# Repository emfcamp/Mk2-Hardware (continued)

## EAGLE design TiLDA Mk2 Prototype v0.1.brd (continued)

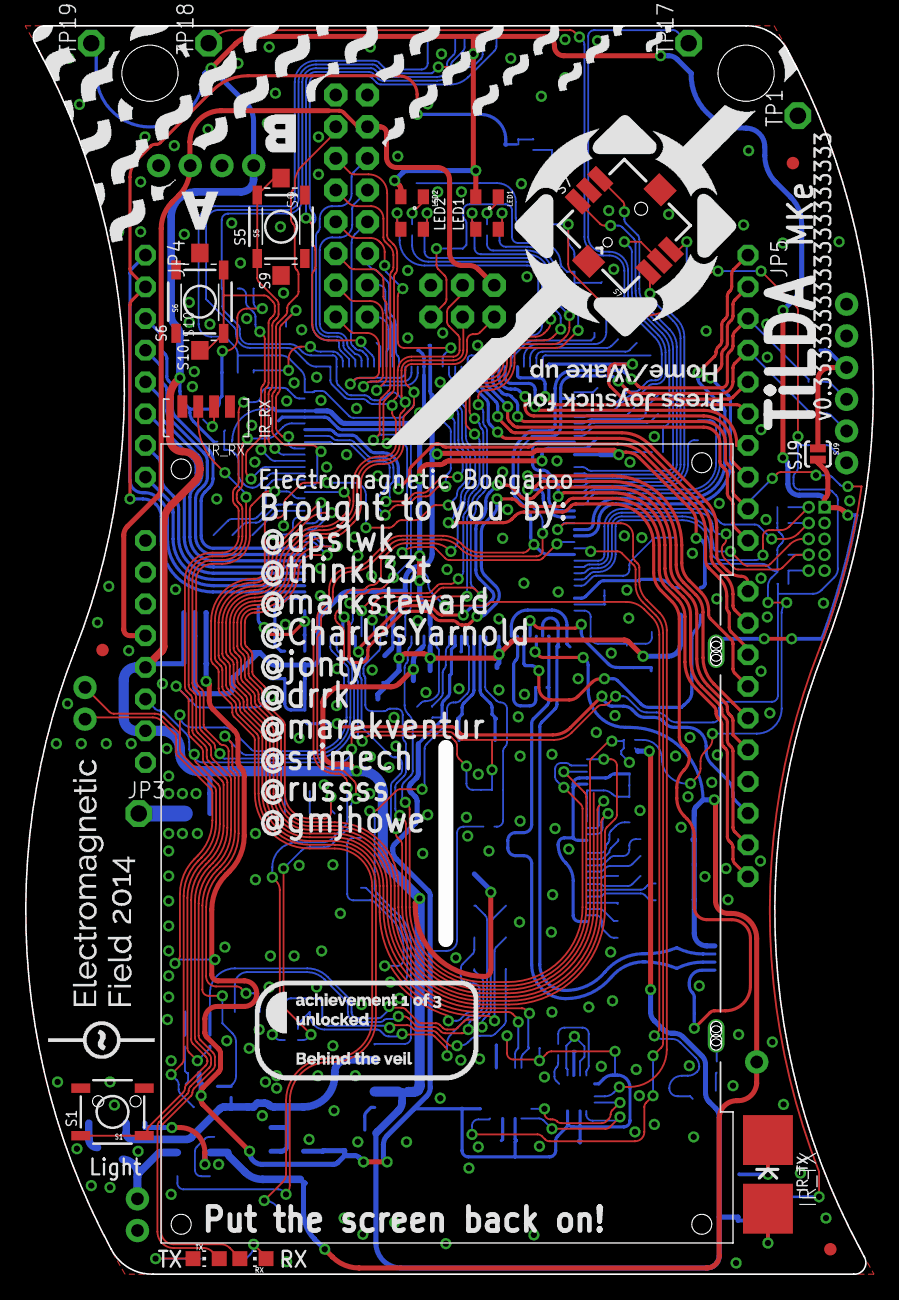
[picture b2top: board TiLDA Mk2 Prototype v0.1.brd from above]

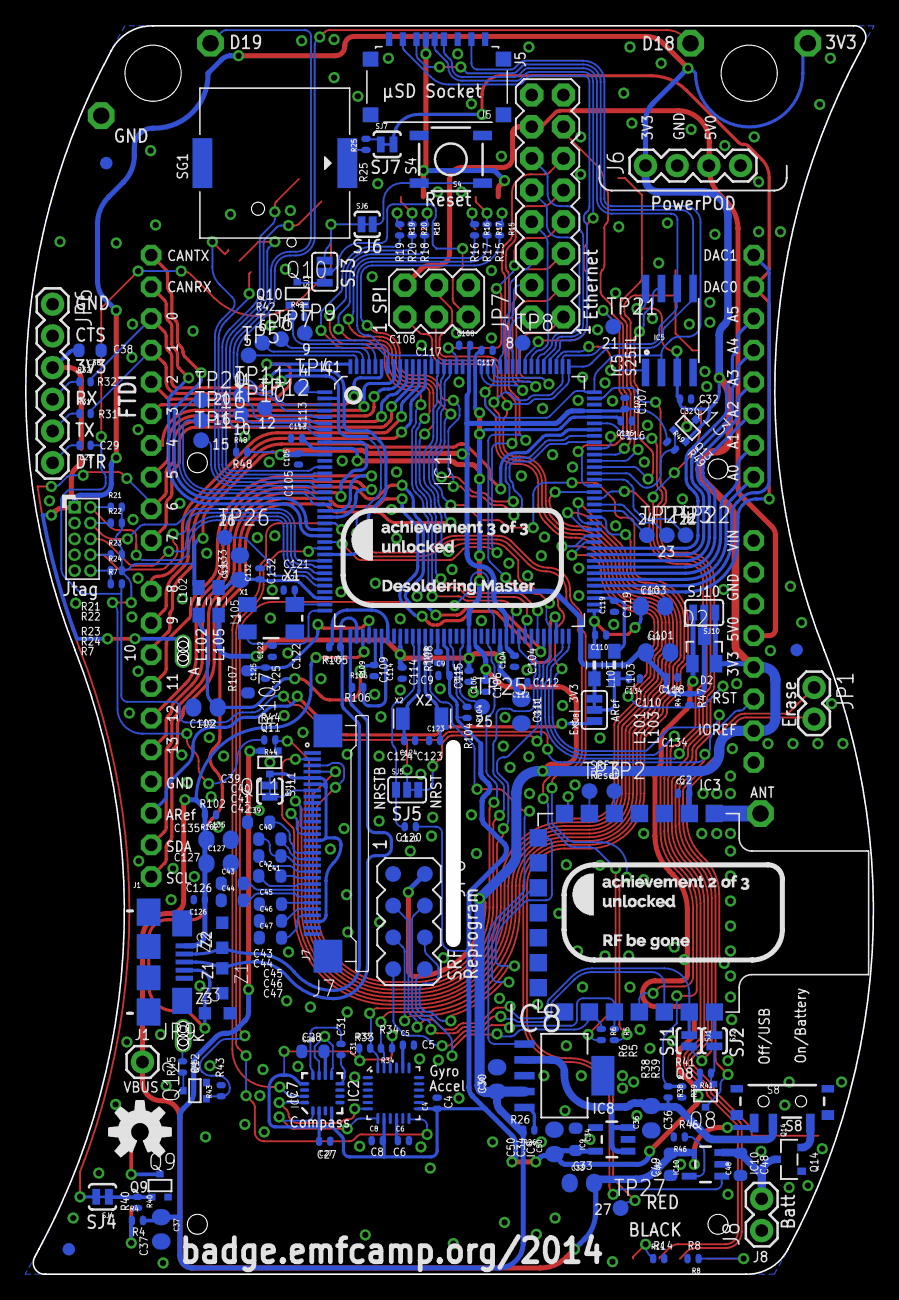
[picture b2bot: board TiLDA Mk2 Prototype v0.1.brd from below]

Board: 4 copper layers, 67.9 x 100.0 mm, 205 parts (177 on the bottom side), 191 nets.

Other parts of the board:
JP9: VBUS; 1X01

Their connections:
VBUS: JP9.1; also elsewhere on the board

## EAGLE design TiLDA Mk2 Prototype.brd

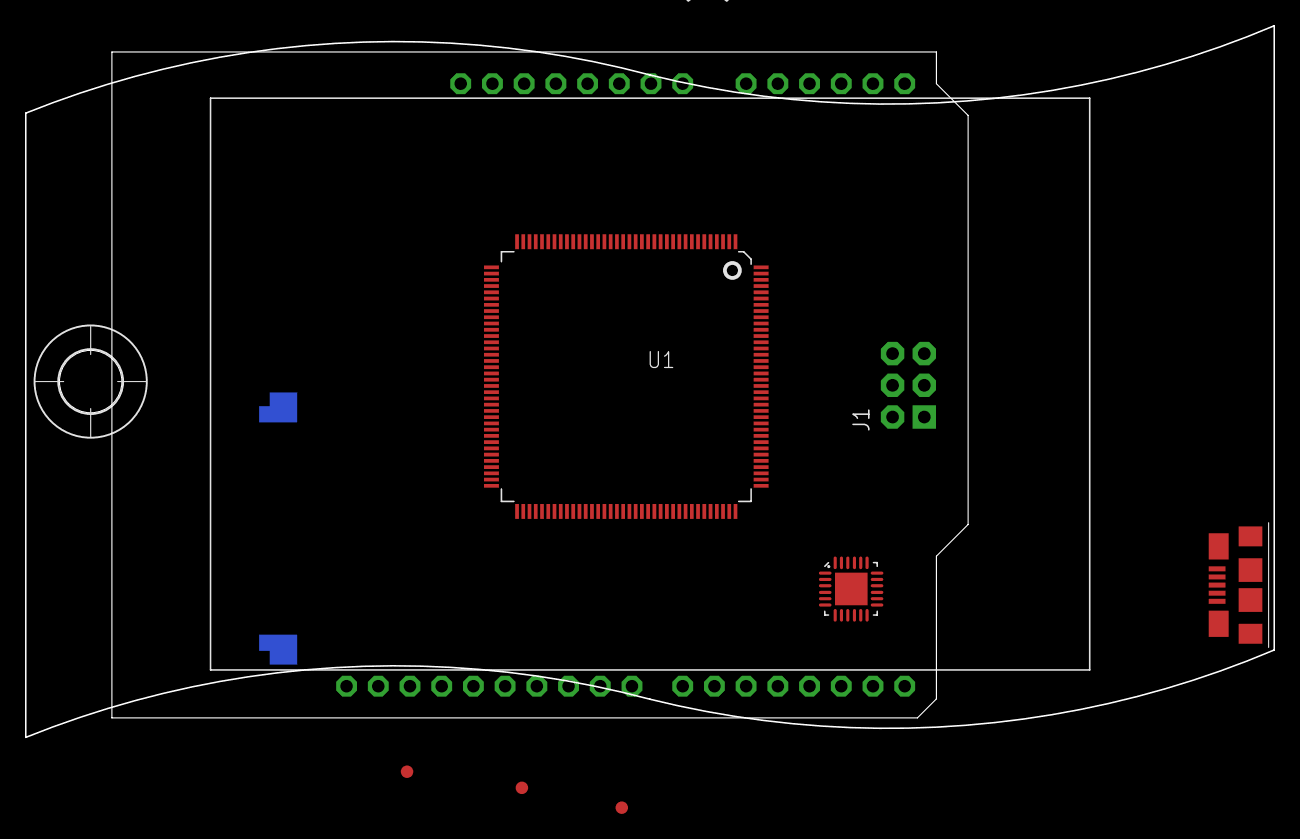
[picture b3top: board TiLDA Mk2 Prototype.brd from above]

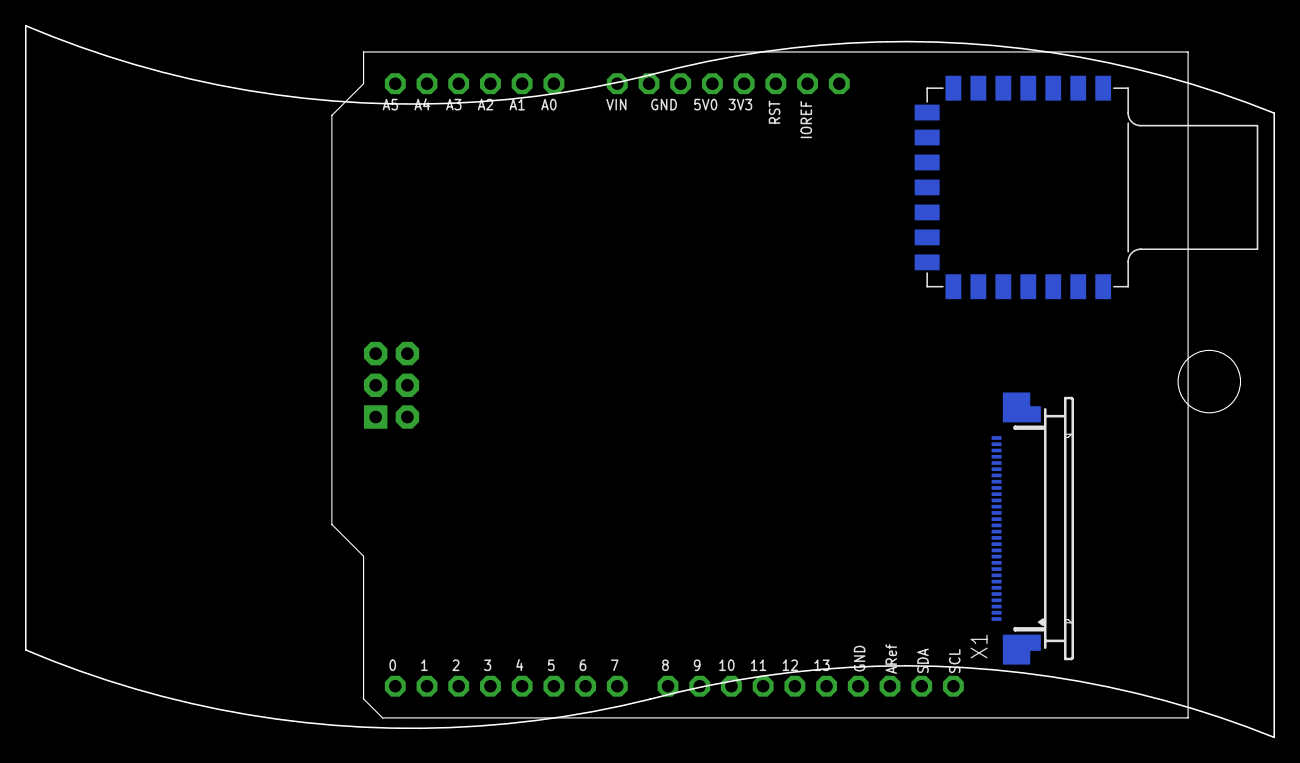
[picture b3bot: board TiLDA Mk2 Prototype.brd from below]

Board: 2 copper layers, 100.0 x 57.0 mm, 16 parts (3 on the bottom side), 5 nets, no tracks yet.

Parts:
H1: MOUNT-HOLE5.0; 5,0
J1: SPARKFUN_AVR_SPI_PRG_6NS; SPARKFUN_2X3-NS
JP1, JP2, JP3: FIDUCIAL1X2.5-STOP; FIDUCIAL-1X2.5-STOP
LOGO1: OSHW-LOGOM; OSHW-LOGO-M
LOGO2: EMFLOGO-BOTH; EMFLOGO
LOGO3: CISECOLOGO-LARGE; CISECO1
U1: ATSAM3X8EA-AU; LQFP144
U2: MPU-6000QFN-24; QFN-24-TESTING
U3: ARDUINOR3-CISECO; ARDUINOR3-LWKTXT
U$1: EPD-OUTLINE-2.7"; EPD-2.7
U$2: TILDA_BOARDOUTLINE; TILDA_BADGEBOARDBARE
U$3: SRF-LANDING-1.0A-MOVE
USB1: SERIAL_MICRO-USB-ZX62-B-5PA; SERIAL_ZX62-B-5PA
X1: 52745-3090

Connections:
GND: U3.GND, U$3.10
GND1: U1.12, U3.GND1, USB1.GND@1
GND2: U1.58, U3.GND2, USB1.GND@2
GND3: U1.106, USB1.GND@3
GND4: U1.126, USB1.GND@4

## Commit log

2013-09-05 Adding Ciseco-Eagle-Library Submodule for SRF footprint
2013-09-05 Adding Parts Library and Blank Prototype Schematic
2013-09-06 Parts: Adding a load of basic parts
2013-09-06 Parts: Adding more basics and Logo's
2013-09-06 Parts: Bunch of changes, adding outline and UCL logo from MK1
2013-11-16 Parts: Lots of changes, Custom EPD Zif Symbol, linked to some std connectors, Adding a load of other stuff
2013-11-16 Parts: Bunch more stuff
2013-11-16 Prototype: Working on board outline and initial layout
2013-11-18 Parts: adding FCI 62684 connector footprint for EPD
2013-11-18 Prototype: working on about and wring some of the EPD support parts
2013-11-20 Parts: Added Battery 55x44 Outline
2013-11-20 Parts: Adding some headers
2013-11-20 Parts: Adding µSD socket footprint
2013-11-20 Prototype: Rotated everything, Started tiding schematic, adding SRF wiring, add µSD footprintt, much more
2013-11-20 Ciseco Footprints: Minor Updates
2013-11-20 Parts: Updating MOSFET footprints
2013-11-20 Parts: MPU Footprint, reworked QFN24 footprint
2013-11-20 Prototype: Working on MPU connections, swapped out for new footprint
2013-11-21 Parts: Short pins on Arduino symbol
2013-11-23 Parts: Adding solder jumpers
2013-11-23 Prototype: Finished MPU Schematic wire up
2013-11-23 Parts & Portotype: Update MPU part's to no die after reading data sheet
2013-11-23 Parts: Adding posible USB AB footprint
2013-11-23 Parts & Prototype: Updating USB footprint
2013-11-23 Parts & Prototype: Move Battery to ref layer
2013-11-23 Parts: Copy in CPOL-EU
2013-11-26 Parts: Adding smaller JST as used in MK1
2013-11-26 Prototype: Swapped Out JST, starting to add some SAM3X support parts
2013-11-26 Ciseco footprints: SRF v1.2 landing update
2013-11-26 Ciseco footprints: Ciseco LOGO update
2013-11-26 Prototype: Lots of wiring on SAM3X
2013-11-27 Parts: Lots of cleaning up
2013-11-27 Prototype: Swapping out some parts moving some stuff around
2013-11-27 Parts: Adding Wuerth inductor
2013-11-27 Prototype: Lots of decoupling
2013-11-27 Prototype: USB TX&RX LED's
2013-11-27 Parts: Cleaning up some silk screen, adding round Cap's and Resistors from Arduino Lib
2013-12-04 Parts: Adding DCDC and Lipo Charger
2013-12-23 Parts: Added SPI EEPROM/Flash footprint, finished up Arduino SPI Footprint, adding varistor for ESD protection
2013-12-25 Parts: Updated mount hole, added http://www.patternagents.com touch pads, and tweaked for 45 version
2013-12-25 Prototype: Lots of changes, Lots of wiring up in schematic, added touch pad’s, swapped SD footprint, wire up LED’s, chosen IR LED, added reset button, moved lots of stuff around, hatched ground area 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
2013-12-26 Prototype: More playing around with touch pad’s
2013-12-26 Parts: Adding Joystick and tweaked to APLS Footprint
2013-12-26 Prototype: Going back to Joystick and buttons
2013-12-26 Prototype: Wired up EPD in schematic, wired up buttons in schematic, placed JTAG Header, swapped out Resistor array for singles, Added reset pin jumper
2013-12-27 Parts: update JTAG and Eth Header outline
2013-12-27 Prototype: Moving some signals around and wiring up a load more devices
2013-12-27 Prototype: Adding FET to ISP RESET pin
2013-12-27 Parts: Adding Fuse footprint from rcl
2013-12-28 Parts: Piezo PKLCS1212E footprint
2013-12-28 Prototype: Update buzzer, looking at moving USB to side (shorter tracks)
2013-12-29 Parts: Adding PMIC, FET, Inductors for FAN5404x
2013-12-29 Prototype: Trying FAN5404x PMIC
2013-12-30 Parts: Adding LTC4160 PMIC, LPS4018 INDUCTOR
2013-12-30 Parts: Updating Slik on Joystick and PLCC2
2013-12-30 Parts: Adding MCP1825T regulator
2013-12-30 Prototype: Adding MCP1825T as 3V3 reg, adding and trying LTC4160 PMIC
2013-12-30 Prototype: Swapping signals to get wakeup pins
2013-12-30 Ciseco footprints: Updating to pull in Power-POD Landings
2013-12-31 Parts: Adding HMC5883L optional compass, M08x2 Header
2013-12-31 Prototype: Adding optional HM5883L Compass footprint. Swapping Ethernet header to match the Tanijino one, should then be able to use there modules, had to move RGB LED’s out for Eth Header
2013-12-31 Parts: Adding TP versions of M04x2
2013-12-31 Prototype: Started wiring up in board, lots todo still
2013-12-31 Prototype: More wiring, Stash before moving Reset button
2013-12-31 Prototype: Reset and JTAG move around
2014-01-01 Prototype: Wiring up, Stash before remove FAN5404X PMIC
2014-01-01 Parts: Schematic Footprint updates
2014-01-01 Prototype: Bunch more wiring, PMIC now in place, Lots of schematic tidying.
2014-01-01 Parts: Adding AT45DB data flash footprints, tweaked some others
2014-01-01 Prototype: Adding alternative SPI FLASH chip and foot print.
2014-01-01 Prototype: Wired up the SPI Flash and SD socket
2014-01-01 Prototpye: JTAG header wired.
2014-01-02 Prototype: More wiring bring signals up from the lower half
2014-01-02 Prototype: USB Data pair routed and length matched
2014-01-02 Prototype Buzzer disconnect jumper
2014-01-02 Prototype: Adding I2C pull-up’s
2014-01-02 Prototype: Reworked USB Traces, tweaked some other bits
2014-01-02 Parts: Reworking IMU Footprints
2014-01-02 Prototype: Updating IMU Footprints,
2014-01-02 Prototype: Swapping MPU_INT onto a wake up pin
2014-01-02 Prototype: Adding Pull-Up’s for PMIC output lines
2014-01-02 Prototype: More wiring
2014-01-03 Prototype: Adding a PD to monitor Batter Voltage
2014-01-03 Prototype: Assigned the last of the Pins, PMIC and HMC
2014-01-03 Prototype: Lots of wiring up, adding Test Pad’s for unused pins
2014-01-04 Prototype: Lots more wiring up, swapped PMIC ILIM signals, moving some other stuff around
2014-01-04 Prototype: More wiring, FWUP pull-up to VBACKUP
2014-01-04 Prototype: Wiring done!!!
2014-01-04 Prototype: Adding name and version to Silk
2014-01-04 Grebers: Adding prototype v0.1
2014-01-04 PDF: Schematic for v0.1
2014-01-05 Parts: Creating EMF Power-POD landing (Custom Silk) Prototype: Updating Power-POD landing
2014-01-05 Parts: Update USB AB Schematic footprint Prototype: Lots of Silkscreen changes, added part placement labels Gerbers: Updated for changes Parts List: Adding txt export of parts list
2014-01-08 Parts: Update Lipo Connector silk
2014-01-08 Parts: Adding slide switch
2014-01-08 Prototype: Adding slide switch
2014-01-10 Prototype: Adding conductive thread pad’s, moving fid’s around, tidy some other bits
2014-01-10 Gerbers: Update to latest
2014-01-11 Parts: Adding alterative µSD socket
2014-01-11 Prototype: New SD Socket in place, adding extra land yard hold, lots to fix up
2014-01-11 Prototype: Correct µSD socket value
2014-01-11 Prototype: Finish off rework to fit two holes tidy up some other traces. Parts: New 4.5mm hole with no silk
2014-01-11 Prototype: Trace tweak
2014-01-12 Parts: restore TILDA outline device, New Battery outlines
2014-01-12 Prototype: Lots of cleaning up, part values, few tracks, Added decoupling for IR TX and FTDI
2014-01-12 Prototype: swap C30 & C35 for 0805
2014-01-12 Prototype: C34, C38 to 10v, C21, C24, C25 to 0603 X5R
2014-01-12 Prototype: Move C120 to NTRSB and VBackup
2014-01-12 Parts: Updating Xtal to add 5x3.2
2014-01-12 Prototype: Update for bigger X1 Crystal
2014-01-12 Prototype: Part Value updates Gerbers: update to latest PDF: update to latest
2014-01-12 Prototype: FTDI Power Jumper
2014-01-14 Prototype: Corrected Joystick pins
2014-01-14 Parts: Tweak buzzer footprint Prototype: Update buzzer footprint and move res to fit
2014-01-16 Gerbers: Final v0.1 prototype version as sent to ragworm
2014-01-16 Adding DRC and CAM rules Gerbers: updated file name extensions to work with gerblook.org
2014-01-21 Prototype: Minor Trace tweak
2014-02-08 Prototype: Adding Pull up/down resistors to FET’s, Schematic only for now
2014-02-08 Prototype: move resistor near target locations
2014-02-08 Prototype: Adding IR_RX_PWR MOSFET and resistor parts
2014-02-16 Prototype: Move pin 1 SPI silk
2014-02-16 Parts: Adding TiLDA Shield
2014-03-29 Prototype: Fitting some of the pull up's
2014-04-27 ProPrototype: More pull up's and FET for IR_RX
2014-06-23 Parts: First pass at adding the LCD outline
2014-06-28 Parts: updating LCD outline
2014-06-28 Prototype: Remove JST socket, throw in 2 pin, add LCD reference,
2014-06-28 Prototype: Remove ePaper parts and outline
2014-06-28 Prototype: remove LPS4018 PMIC
2014-06-28 Parts: SFV30R-2STE1HLF connector for LCD
2014-06-28 Prototype: move out USB and IMU, adding in LCD and wiring up cap's
2014-06-28 Parts: Adding 0805 Round to cap pol
2014-06-28 Prototype: update caps to 0805 foot print to get some space back
2014-06-28 Prototype: It fits!! lcd slot and connector in place and lots of traces moved around
2014-06-29 Parts: adding new tac switch
2014-06-30 Parts: Quick and dirty 30way bottom FPC
2014-07-05 Quick LCD breakout for new LCD
2014-07-05 Parts: LCD reference outline
2014-07-05 Parts: Minor silk fix
2014-07-05 Prototype: Lots of changes
2014-07-05 Parts: Tac switch silk tweak
2014-07-05 Prototype: More wiring up. moved IR_RX around, lost PowerPOD
2014-07-06 Prototype: Lots more wiring done, IMU reconnected, just LCD left
2014-07-06 Parts: M02 tweak
2014-07-06 Prototype: Finished rewire
2014-07-07 Prototype: Last tweak for v0.2, adding SJ for VDDIO between 3V3 and VBACKUP
2014-07-07 Prototype: Moved silk screen back over
2014-07-07 Gerbers: v0.2
2014-07-07 Gerbers: Archive for v0.2
2014-07-10 Parts: Miter corner board Prototype: Miter corner board
2014-07-10 Prototype: Slik screen updates
2014-07-10 Prototype: moved SRF reprogram to the bottom, more silk screen tweaks
2014-07-12 Parts: correct LCD FPC and outline footprints
2014-07-13 Prototype: fixed LCD conections
2014-07-13 Prototype: Typo
2014-07-15 Prototype: Curve all the tracks
2014-07-16 Prototype: more curves
2014-07-16 Prototype: Allow power from just USB
2014-07-16 Prototype: Even more curves
2014-07-16 Prototype : Flipped IR_RX around for easier hand soldering
2014-07-17 Prototype: Tweaks
2014-07-17 Parts: Joystick footprint Prototype: Joystick footprint
2014-07-17 Parts: Fix LCD footprint Prototype: Correct tracks fro LCD Footprint
2014-07-17 Prototype: 0805 LED's
2014-07-18 Prototype: Minor tweaks, adding TP27, moved L102, L105
2014-07-19 Prototype: Get backlight onto a PWM, swapped LCD_BACKLIGHT and TP25.
2014-07-19 Prototype: Get LIGHT on to a wake up pin, swapped LIGTH with AT_COMMAND
2014-07-19 Prototype: Artwork and trace tweak
2014-07-20 Prototype: VDDIO rewire
2014-07-20 Prototype: Reverser polarity protection
2014-07-20 PDF: Add missing v0.2 schematic
2014-07-20 Prototype: Minor schematic tweaks, board tweaks
2014-07-20 Prototype: Adding pull up to LCD D0-D5 via SJ11
2014-07-20 Prototype: Last few curved traces
2014-07-20 PDF: Versino 0.33333333
2014-07-20 Parts and Prototype: Final artwork
2014-07-20 Gerbers: Artwork
2014-07-21 Parts and Prototype: Adding BAT54C to VDDIO
2014-07-21 Gerbers: Updated
2014-07-21 Prototype: Correct Schematic Merge
2014-07-21 PDF, Gerbers: Updated
2014-07-21 All: Last tweak to add VBus pad for OTG stuff
2014-07-21 Zip's: Version 0.333 sent to ragwrom
2014-07-31 Gerbers: Tweak to correct top stencil
2014-08-12 Parts: Updating MOSFET SOT23 footprints for next time
2014-11-05 Parts: Updating USB-AB to split GND and Shield pins
2014-11-06 Parts: Adding SOT523 to MOSFET-N
2015-05-12 Parts: IR footprint for both TT and TR
2015-05-12 PDF: renames and mount data
2015-05-12 Parts: Miter shield outlines, add logo artwork
2015-05-12 Parts: Add Shield double headers version
2015-05-12 Parts: prototype headers
2015-05-12 ProtoShield: First Commit
2015-05-13 Parts: update shield, and adding various pats for PorotoShield
2015-05-13 ProtoShield: lots more work
